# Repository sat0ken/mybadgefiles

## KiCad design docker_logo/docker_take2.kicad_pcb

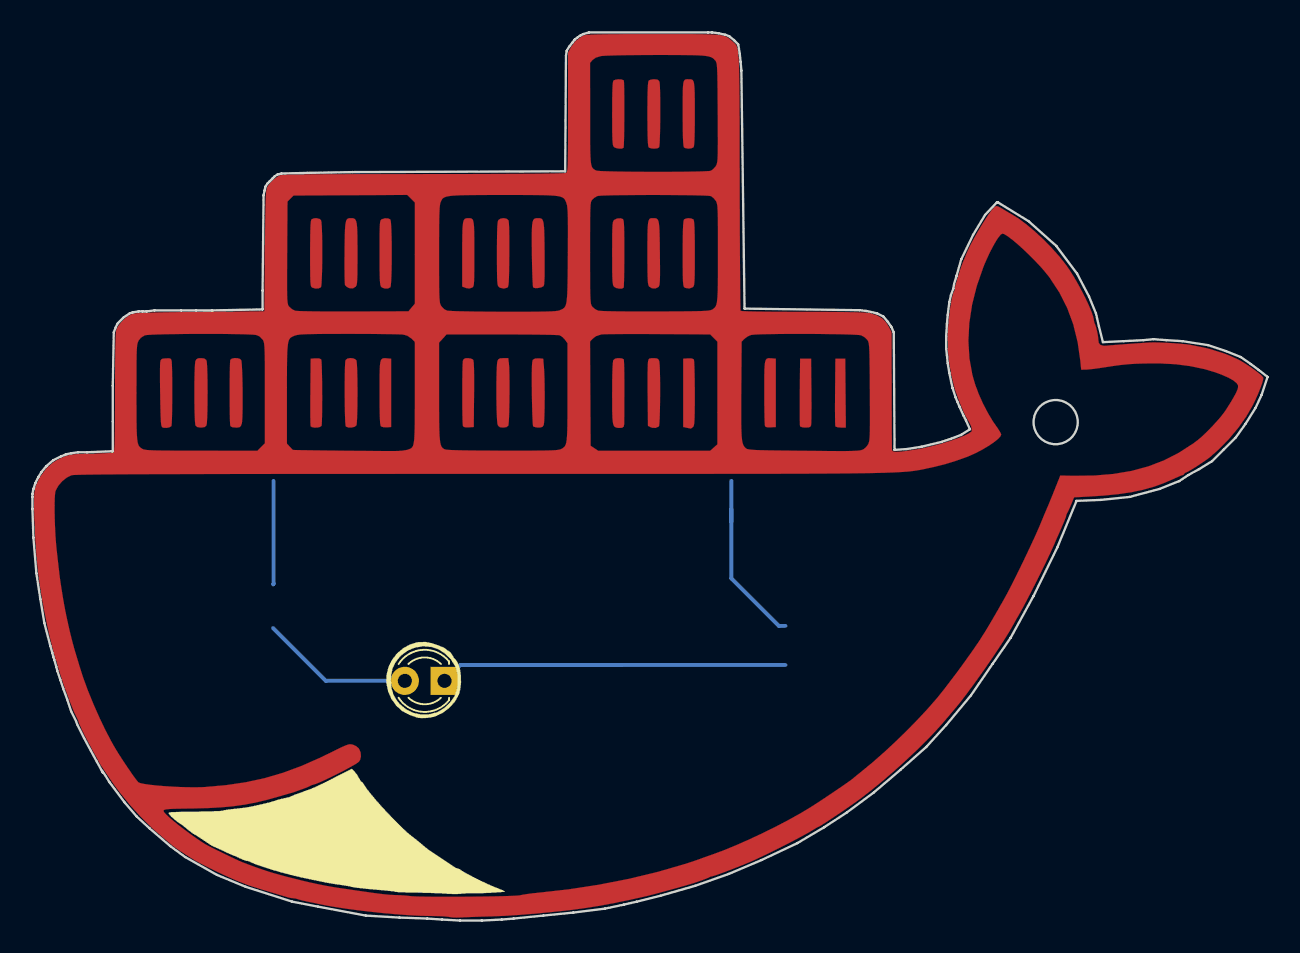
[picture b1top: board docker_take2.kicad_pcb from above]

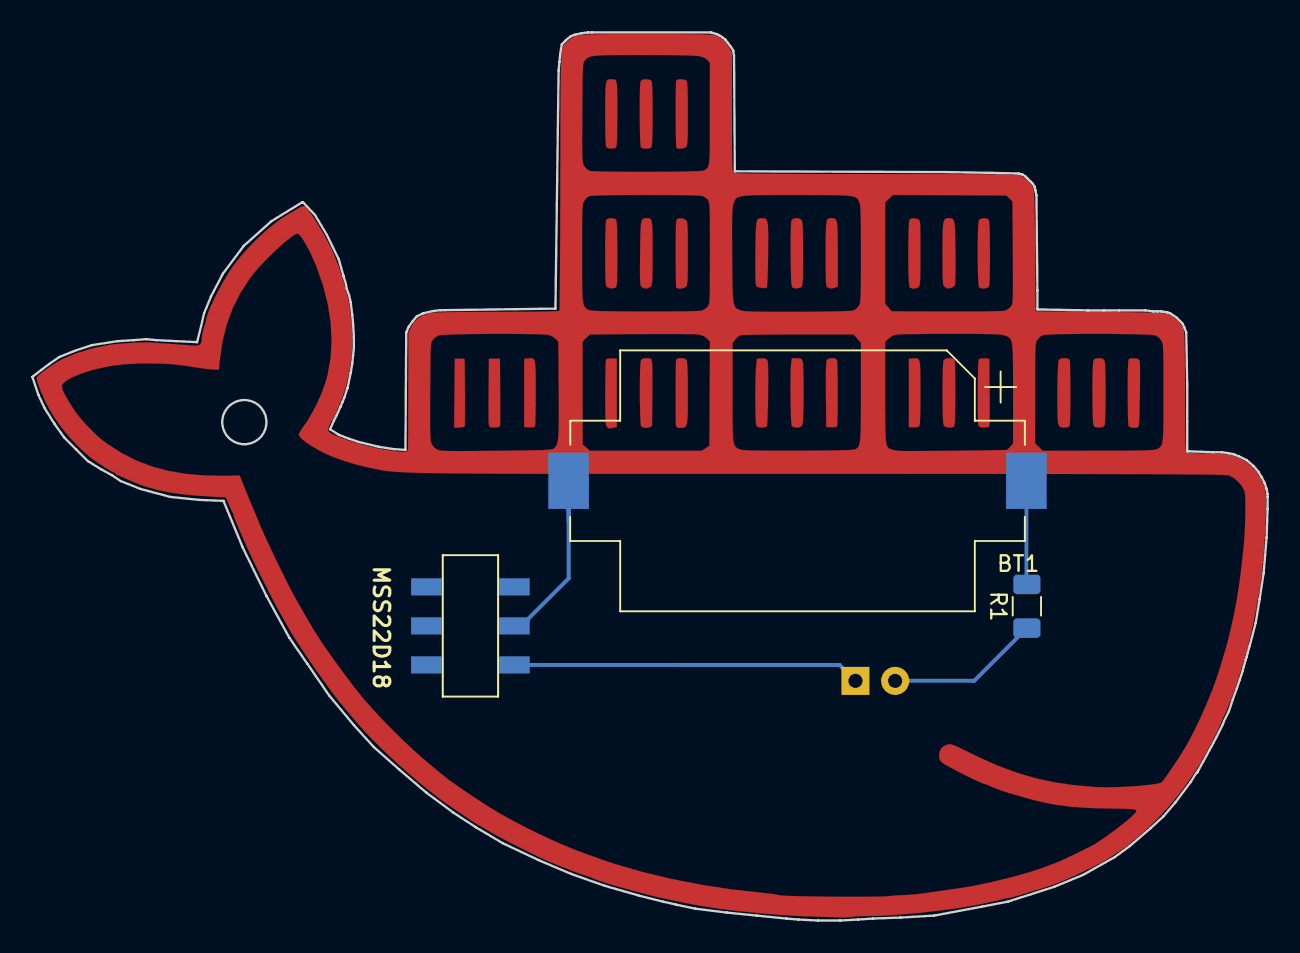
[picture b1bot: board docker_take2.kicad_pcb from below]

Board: 2 copper layers, 79.1 x 56.8 mm, 4 parts (3 on the bottom side), 4 nets.

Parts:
BT1: Battery_Cell; BatteryHolder_Keystone_1060_1x2032
D1: LED; LED_D3.0mm
R1: 470; R_1206_3216Metric
SW1: MSS22D18

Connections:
unnamed: BT1.1, R1.2
unnamed: BT1.2, SW1.P1
unnamed: D1.1, SW1.T1B
unnamed: D1.2, R1.1

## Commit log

2019-07-17 add docker logo files
2019-07-17 github logo files
2019-07-17 add k8s logo files
2019-07-17 modify README.md
2019-07-17 modify file name
